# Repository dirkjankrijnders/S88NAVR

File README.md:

S88NAVR
=======

An implementation of the S88-N protocol for Atmel Atmega[8/48/88/168/328] microcontrollers. So far, an Arduino Pro Mini version and the actual board have been tested.

Goal
----

The goal is the make small, cheap reliable feedback modules for the S88 system. Hence choice for the microcontroller, one IC instead of the three discreet ones. The choice for SMD technology for a small board with components on both sides, as most will be hand soldered. The reliability comes from the use of the S88-N Cabling and timing, input diodes and a RC input network. If wanted the RC network and diodes can be short to minimize cost when needed, leaving 10 components (2 connectors, an uc, two caps and five resistors). The RC-network kills spike, the 1N4148 does the same ensuring the reliability of the detection, the big diode make sure the "detection" rail acts a as a ground return as well ensuring reliable operation of the track. 
The board is designed for production by cheap production houses like seeedstudio's PCB service. Goal is to stay under €5.00 for the fully build PCB.

State
-----
The parts for the first revision (Rev. 0) have been ordered, including the PCB at Seeedstudios. See below for an image and a BOM of the non-standard parts.
. The total is still enough under €5.00 to fit the passives and stand-offs (no prices because then come from my stock).
<table>
<tr>
<th>Part</th><th>#</th><th>Conrad #</th><th>price* (€)</th>
</tr>
<tr><td>IC1</td><td>1</td><td>154273</td><td>2.41</td></tr>
<tr><td>P2,P3</td><td>2</td><td>731817+731830</td><td>0.71</td></tr>
<tr><td>J1,J2</td><td>2</td><td>716232</td><td>0.58</td></tr>
<tr><td>PCB</td><td>1</td><td>Seeed</td><td>0.64</td></tr>
<tr><td colspan=3>Total</td><td>4.34</td></tr>
</table>
*When ordering 10+ quantities

The boards came back from Seeedstudios and they work, only one small issue where a track was not connected, update in as rev 0.1. Only in the kicad files, the change is too small to spin a new board.
LICENSE
-------

Both hardware and firmware are placed under the Creative Commons Attribution-ShareAlike 3.0 Unported License. See <http://creativecommons.org/licenses/by-sa/3.0/> and License.txt for more details.

Copyright 2013
Dirkjan Krijnders
<dirkjan@krijnders.net>

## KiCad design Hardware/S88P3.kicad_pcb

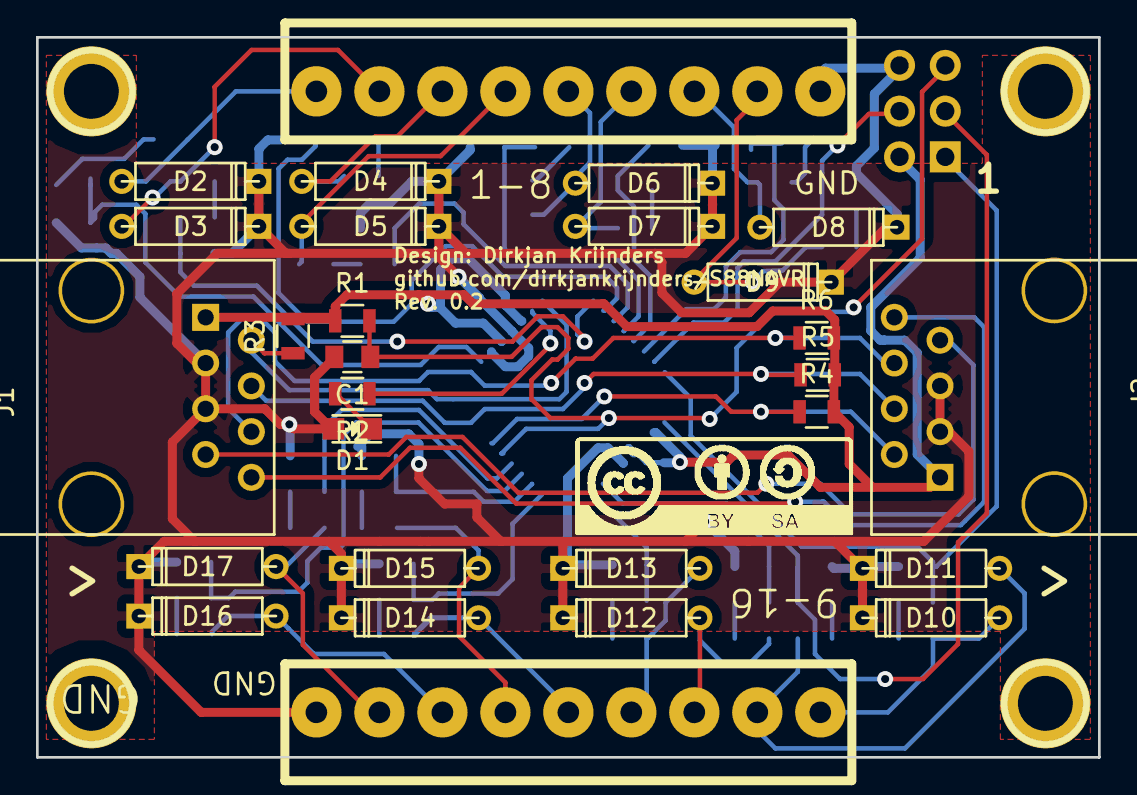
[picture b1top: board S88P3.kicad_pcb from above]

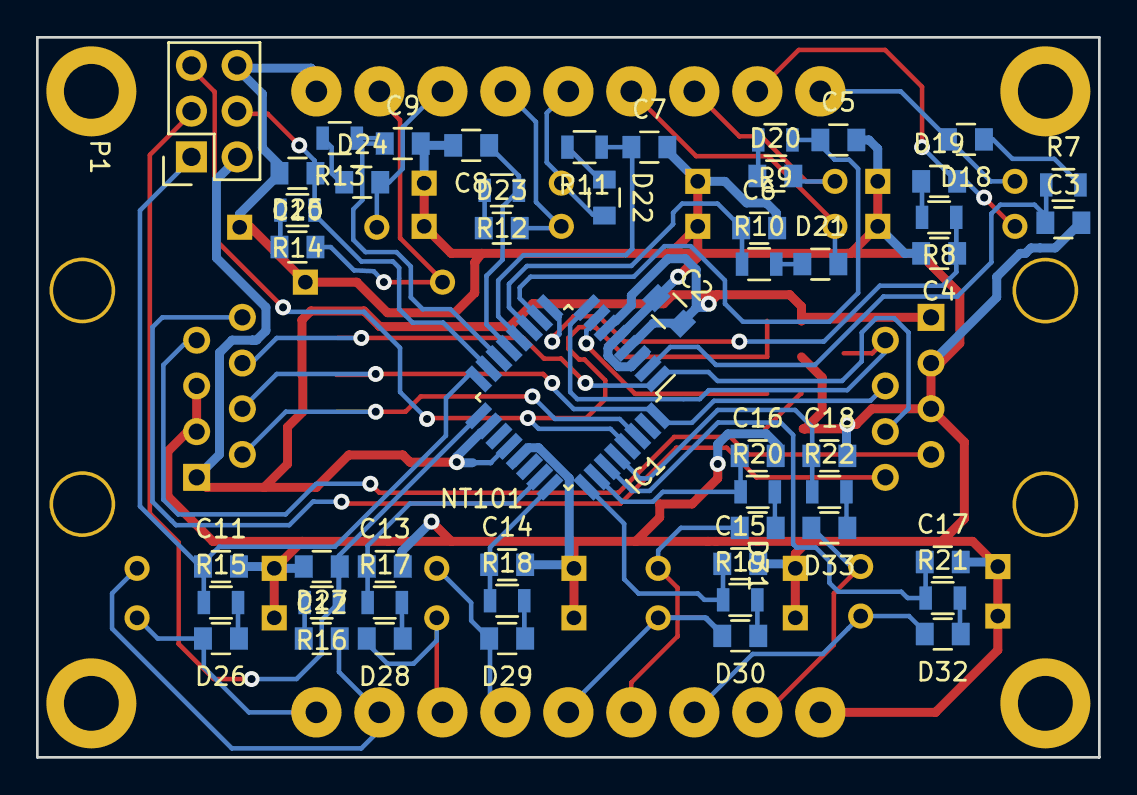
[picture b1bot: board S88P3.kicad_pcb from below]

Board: 2 copper layers, 59.0 x 40.0 mm, 80 parts (52 on the bottom side), 60 nets.

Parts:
C1, C2: 100n; C_0805
C3, C4, C5, C6, C7, C8, C9, C10, C11, C12, C13, C14, C15, C16, C17, C18: 10n; C_0805
D1: LED; LED-0805
D2, D3, D4, D5, D6, D7, D8, D9, D10, D11, D12, D13, D14, D15, D16, D17: 1N4004; D3
D18, D19, D20, D21, D22, D23, D24, D25, D26, D27, D28, D29, D30, D31, D32, D33: 1N4148; C_0805
IC1: ATMEGA8-AI; TQFP-32_7x7mm_Pitch0.8mm
J1, J2: RJ45; RJ45_8
NT101: Nettie; nettie_0.3mm
P1: CONN_3X2; Socket_Strip_Straight_2x03
P2, P3: CONN_8; 9PIN_SC_RM3.5
R1, R2, R3, R4, R5, R6: 10k; R_0805
R7, R8, R9, R10, R11, R12, R13, R14, R15, R16, R17, R18, R19, R20, R21, R22: 1k; R_0805

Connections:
/RAILDATA: J1.8, J2.8
/S88CLOCK: IC1.32, J1.4, J2.4, R5.1
/S88LOAD: IC1.1, J1.6, J2.6, R6.1
/S88OUT: IC1.30, J2.2, R4.1
/S88RST: J1.7, J2.7
/TRACK1: C3.1, IC1.2, R7.1
/TRACK2: C4.1, IC1.9, R8.1
/TRACK3: C5.1, IC1.10, R9.1
/TRACK4: C6.1, IC1.11, R10.1
/TRACK5: C7.1, IC1.12, R11.1
/TRACK6: C8.1, IC1.13, R12.1
/TRACK7: C9.1, IC1.14, R13.1
/TRACK8: C10.1, IC1.15, P1.4, R14.1
/TRACK9: C11.1, IC1.16, P1.1, R15.1
/TRACK10: C12.1, IC1.17, P1.3, R16.1
/TRACK11: C13.1, IC1.23, R17.1
/TRACK12: C14.1, IC1.24, R18.1
/TRACK13: C15.1, IC1.25, R19.1
/TRACK14: C16.1, IC1.26, R20.1
/TRACK15: C17.1, IC1.27, R21.1
/TRACK16: C18.1, IC1.28, R22.1
GND: C1.2, C2.1, C3.2, C4.2, C5.2, C6.2, C7.2, C8.2, C9.2, C10.2, C11.2, C12.2, C13.2, C14.2, C15.2, C16.2, C17.2, C18.2, D1.2, D2.1, D3.1, D4.1, D5.1, D6.1, D7.1, D8.1, D9.1, D10.1, D11.1, D12.1, D13.1, D14.1, D15.1, D16.1, D17.1, IC1.3, IC1.5, IC1.21, J1.3, J1.5, J2.3, J2.5, P1.6, P2.9, P3.9
unnamed: C1.1, IC1.29, P1.5, R1.2
unnamed: D1.1, R2.2
unnamed: D10.2, D26.2, P3.1
unnamed: D11.2, D27.2, P3.2
unnamed: D12.2, D28.2, P3.3
unnamed: D13.2, D29.2, P3.4
unnamed: D14.2, D30.2, P3.5
unnamed: D15.2, D31.2, P3.6
unnamed: D16.2, D32.2, P3.7
unnamed: D17.2, D33.2, P3.8
unnamed: D18.1, R7.2
unnamed: D2.2, D18.2, P2.1
unnamed: D19.1, R8.2
unnamed: D3.2, D19.2, P2.2
unnamed: D20.1, R9.2
unnamed: D4.2, D20.2, P2.3
unnamed: D21.1, R10.2
unnamed: D5.2, D21.2, P2.4
unnamed: D22.1, R11.2
unnamed: D6.2, D22.2, P2.5
unnamed: D23.1, R12.2
unnamed: D7.2, D23.2, P2.6
unnamed: D24.1, R13.2
unnamed: D8.2, D24.2, P2.7
unnamed: D25.1, R14.2
unnamed: D9.2, D25.2, P2.8
unnamed: D26.1, R15.2
unnamed: D27.1, R16.2
unnamed: D28.1, R17.2
unnamed: D29.1, R18.2
unnamed: D30.1, R19.2
unnamed: D31.1, R20.2
unnamed: D32.1, R21.2
unnamed: D33.1, R22.2
unnamed: IC1.7, R2.1
unnamed: IC1.20, NT101.2
S88IN: IC1.8, J1.2, R3.1
VCC: C2.2, IC1.4, IC1.6, IC1.18, J1.1, J2.1, NT101.1, P1.2, R1.1, R3.2, R4.2, R5.2, R6.2

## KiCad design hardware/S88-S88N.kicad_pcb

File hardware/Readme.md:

Making production gerbers
=========================

Exporting gerbers from kicad
----------------------------
To create gerbers for a PCB, open the .brd or .kicad\_pcb file in pcbnew. Choose "plot" from the "file" menu. Set the output directory to "Outputs/Rev_x" where x is the current revision number. Also create a drill file is that same directory, with the following settings:

- Units: Inch
- Suppress leading zeros
- Drill Map File Format: Gerber
- No options checked
- Drill origin: Absolute

You should now have at least 6 gerbers and a drill file in the "Outputs/Rev_x" directory.

Merging gerbers into a panel
----------------------------

Install gerbmerge (<http://ruggedcircuits.com/gerbmerge/>). Check the settings in "template_main", especially the revision number in the path. Then generate the gerbmerge config file use the script:

`./make-gerbmerge-config.sh S88-S88N S88P3 >> gerbmerge-config`

Where the last arguments are the basename of the gerbers made in the previous step. Make adjustments to the panel-layout as needed and create the merged gerbers:

`python2.7 ~/Projects/3rd_party/gerbmerge-1.8/gerbmerge/gerbmerge.py gerbmerge-config panel-layout`

The drill file created by gerbmerge are very minimal and not every program likes them, so fix the .xln with the supplied script:

`./gerbmergexln2drl.sh S88-Panel-Rev0`

where the last argument is the basename of the panel gerbers.

Checking the results
--------------------
check the results with gerbv:

`gerbv <basename>.*`

double check with gerbview:

`gerbview <basename>.*`

triple with an online gerber viewer:

- <http://mayhewlabs.com/3dpcb>

If the output of all programs looks good, you're in good shape for production!

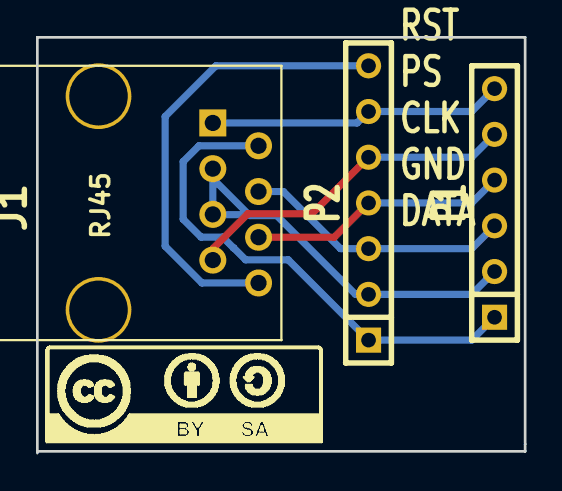
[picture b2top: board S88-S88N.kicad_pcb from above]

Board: 2 copper layers, 27.1 x 23.1 mm, 3 parts (0 on the bottom side), 7 nets.

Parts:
J1: RJ45; RJ45_8
P1: CONN_6; SIL-6
P2: CONN_6; SIL-7

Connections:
unnamed: J1.6, P1.4, P2.4
unnamed: J1.7, P1.5, P2.5
unnamed: J1.1, P1.6, P2.6
unnamed: J1.8, P2.7
unnamed: J1.2, P1.1, P2.1
unnamed: J1.3, J1.5, P1.2, P2.2
unnamed: J1.4, P1.3, P2.3

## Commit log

2013-01-20 Arduino Pro Mini version
2013-01-20 Added README
2013-01-20 Added licensing information
2013-01-22 First full schematic and board layout
2013-01-23 - Cleaned up board - Added ground plane - Added CC-BY-SA logo - Added information text
2013-01-23 - Added schematic for converter board
2013-01-23 Added board and support files for converter board
2013-01-23 Updated Silkscreen
2013-01-23 Added standoff holes
2013-01-25 Files to generate the production gerbers
2013-01-25 Made the board slightly less wide, added arrows on silkscreen
2013-01-25 Annotated schematic
2013-01-27 Added goal description to the readme
2013-01-27 Updated gitignore
2013-01-27 Add comments to the code
2013-01-27 Added image of the pcb panel for Rev.0
2013-01-27 Added the zip-file with the production files for Rev. 0
2013-01-27 Added current state of the project
2013-01-27 Cropped the image
2013-01-27 Completed current state
2013-01-27 More on the reliability
2013-01-27 Gerber and panel creation manual
2013-01-28 Added pdf of rev 0 schematic
2013-02-01 New Makefile and matching .gitignore
    Based on:
    http://www.nongnu.org/avr-libc/user-manual/group__demo__project.html
2013-02-02 Arduino wants its files in a directory with the same name
2013-02-02 Initial implementation of S88 to UART bridge
2013-02-06 Start of UART implementation
2013-02-18 - #def'd the S88 pins
2013-02-18 - Cleanup\r- Used pin definitions
2013-02-18 Rename c file to reflect μc use
    Flash LED
2013-02-19 Cleanup
2013-02-19 Fixed short between GND and Data
2013-02-22 Added assembler version of firmware
2013-02-22 Cleanup and some speedup
2013-02-24 First tested working version!
2013-02-25 Switched low/high around in the buffer...
2013-02-25 Implemented in the input part
2013-03-12 Fixed a missing trace. Fixes #1
2013-03-13 Updated revision number on board
2013-03-13 Moved via to make more room for ADC stuff
2013-03-13 - Fixed comment character
2013-03-15 - Changed terminals to 3.5mm RM to make more room
2013-03-15 Start of converter redesign
2013-03-15 Start of ADC firmware
2013-03-15 Gave the ISP connector more room
2013-03-15 Fixed some silkscreen labels
2013-03-16 Fixed remaining silkscreen labels
2013-03-23 Added FTDI Header, decoupled AVREF and added buffer cap on the power line
2013-03-31 Swapping buffers
2013-04-01 Convinience scripts for uploading
2013-04-01 Added kicad component cache
2013-04-01 Start of debounce implementation
2013-04-01 Ignore some more files
2013-04-01 Fixed shift bug
2013-04-15 Experiments in debounce
2013-04-15 Implemented working byte debounce
2014-09-24 Schematic cleanup
2015-12-07 Updates for newer standard schematic symbols
2015-12-07 Kicad cache and rescue libs update
2015-12-07 Rely on general avrdude configuration for programmer information
2015-12-07 Project file
2016-12-20 Removed “special” library which is not available anymore and not used anyway
2016-12-20 Fixed capacitors and resistor connections
2016-12-20 More connections and a net tie, ERC now passes
2016-12-20 New netlist reflecting recent changes and new version
2016-12-20 Rename and update
2016-12-20 Fixed footprints
2016-12-20 Format upgrade
2016-12-20 Finished component modernisation
